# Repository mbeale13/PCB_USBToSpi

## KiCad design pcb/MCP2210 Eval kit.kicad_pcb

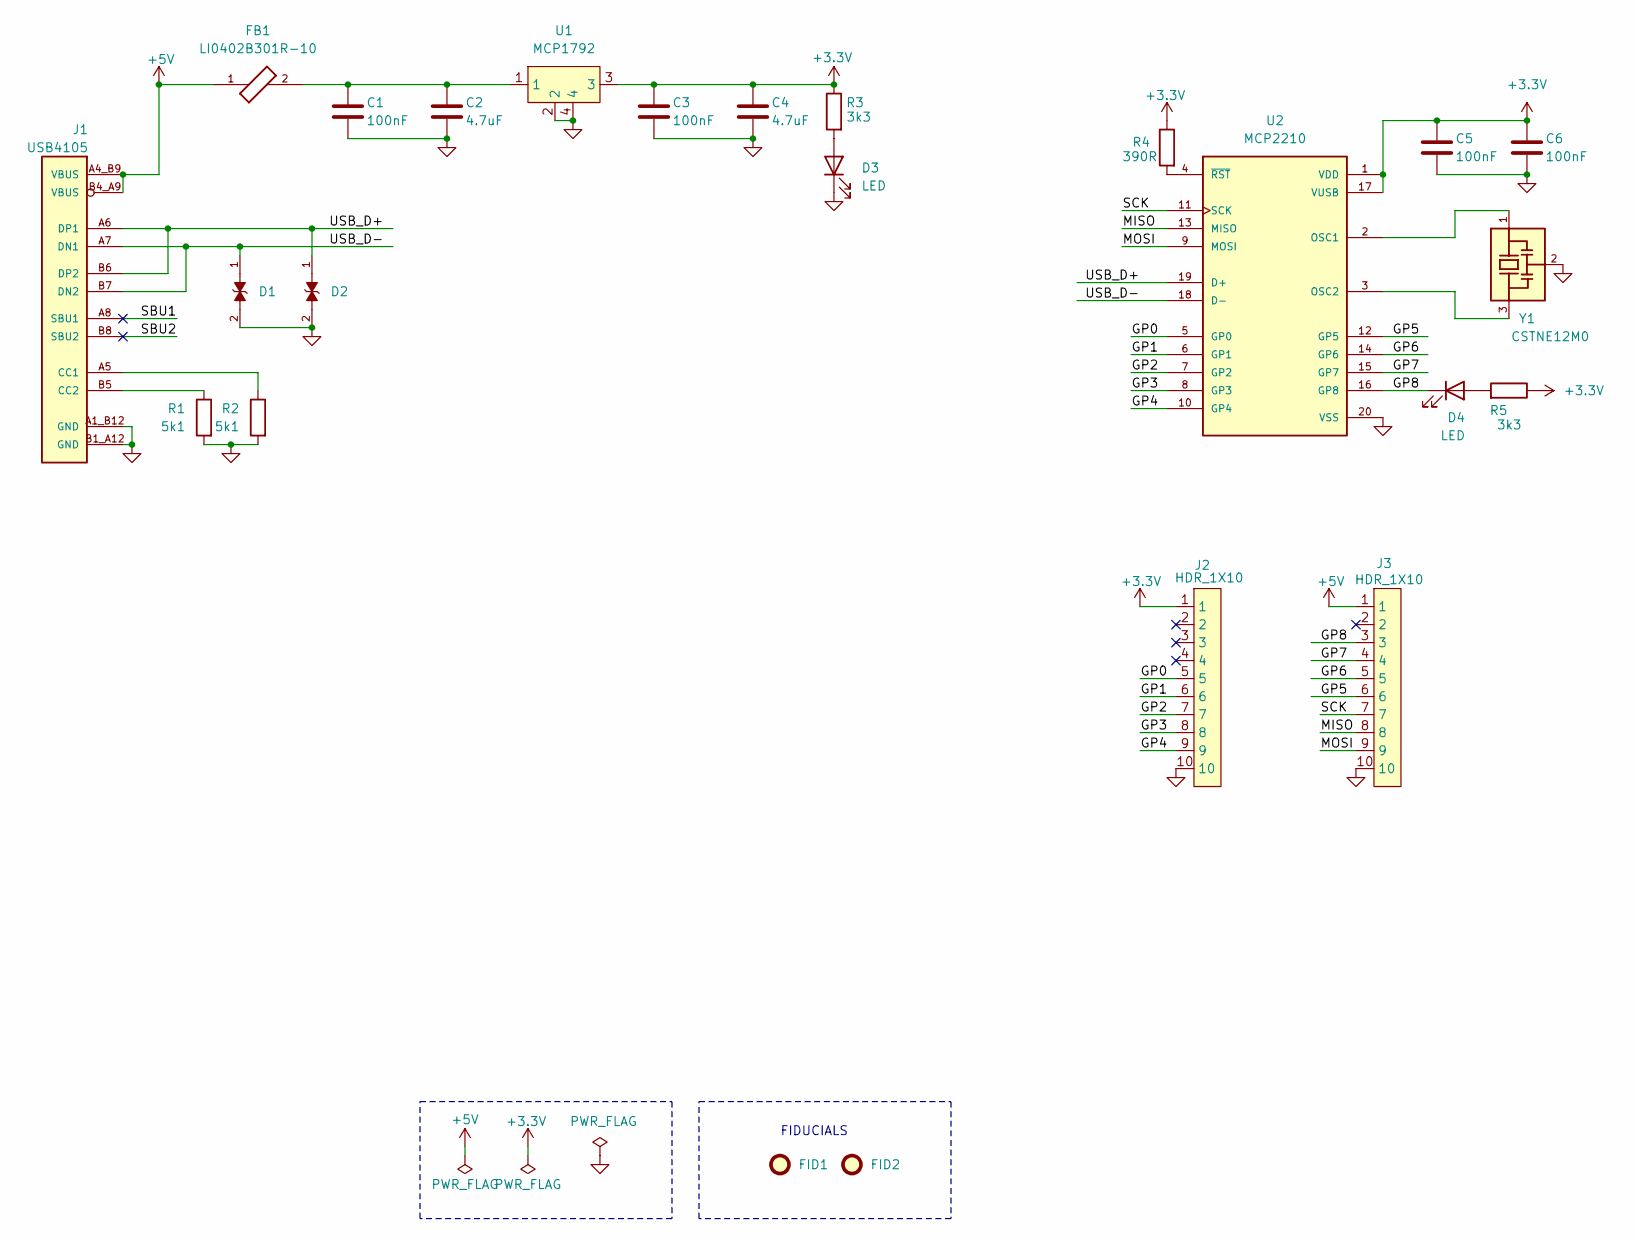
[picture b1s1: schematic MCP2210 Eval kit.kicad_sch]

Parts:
C1, C3, C5, C6: 100nF; C_0402
C2, C4: 4.7uF; C_0603
D1, D2: PGB1010603MR; TRANZORB 0603
D3, D4: LED; LED_0402
FB1: LI0402B301R-10; FERRITE_BEAD_0402
FID1, FID2: Fiducial; Fiducial_0.5mm_Mask1mm
J1: USB4105; GCT_USB4105GFA
J2, J3: HDR_1X10; HDRSRST10P100MIL
R1, R2: 5k1; R_0402
R3, R5: 3k3; R_0402
R4: 390R; R_0402
U1: MCP1792; SOT-223
U2: MCP2210; SSOP-20
Y1: CSTNE12M0; CERRESN

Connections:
+3.3V: C3.1, C4.1, C5.1, C6.1, J2.1, R3.1, R4.1, R5.1, U1.3, U2.1 (VDD), U2.17 (VUSB)
+5V: FB1.1, J1.A4_B9 (VBUS), J1.B4_A9 (VBUS), J3.1
/GP0: J2.5, U2.5 (GP0)
/GP1: J2.6, U2.6 (GP1)
/GP2: J2.7, U2.7 (GP2)
/GP3: J2.8, U2.8 (GP3)
/GP4: J2.9, U2.10 (GP4)
/GP5: J3.6, U2.12 (GP5)
/GP6: J3.5, U2.14 (GP6)
/GP7: J3.4, U2.15 (GP7)
/GP8: D4.1 (K), J3.3, U2.16 (GP8)
/MISO: J3.8, U2.13 (MISO)
/MOSI: J3.9, U2.9 (MOSI)
/SBU1: J1.A8 (SBU1)
/SBU2: J1.B8 (SBU2)
/SCK: J3.7, U2.11 (SCK)
/USB_D+: D2.1, J1.A6 (DP1), J1.B6 (DP2), U2.19 (D+)
/USB_D-: D1.1, J1.A7 (DN1), J1.B7 (DN2), U2.18 (D-)
GND: C1.2, C2.2, C3.2, C4.2, C5.2, C6.2, D1.2, D2.2, D3.1 (K), J1.A1_B12 (GND), J1.B1_A12 (GND), J1.SH1 (GND), J1.SH2 (GND), J1.SH3 (GND), J1.SH4 (GND), J2.10, J3.10, R1.2, R2.2, U1.2, U1.4, U2.20 (VSS), Y1.2
unnamed: C1.1, C2.1, FB1.2, U1.1
unnamed: D3.2 (A), R3.2
unnamed: D4.2 (A), R5.2
unnamed: J1.A5 (CC1), R2.1
unnamed: J1.B5 (CC2), R1.1
unnamed: U2.2 (OSC1), Y1.1
unnamed: U2.3 (OSC2), Y1.3
unnamed: R4.2, U2.4 (~RST)

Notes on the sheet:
FIDUCIALS

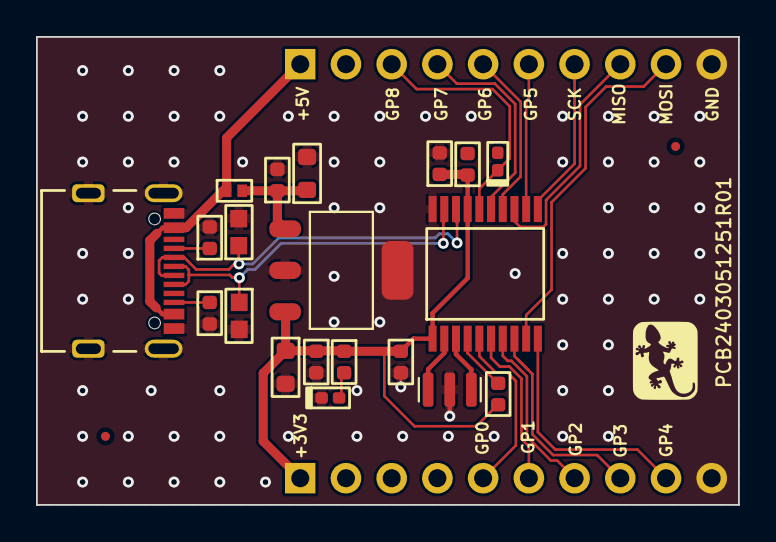
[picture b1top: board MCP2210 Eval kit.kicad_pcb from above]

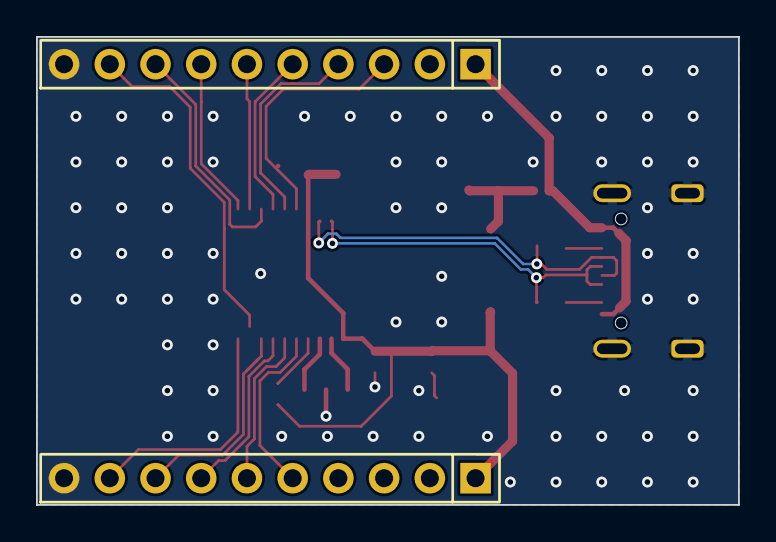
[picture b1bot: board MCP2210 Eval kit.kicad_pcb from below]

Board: 2 copper layers, 39.0 x 26.0 mm, 25 parts (2 on the bottom side), 25 nets.

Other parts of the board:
Gecko1: Gecko_logo; Gecko_logo 5mm x 7mm
